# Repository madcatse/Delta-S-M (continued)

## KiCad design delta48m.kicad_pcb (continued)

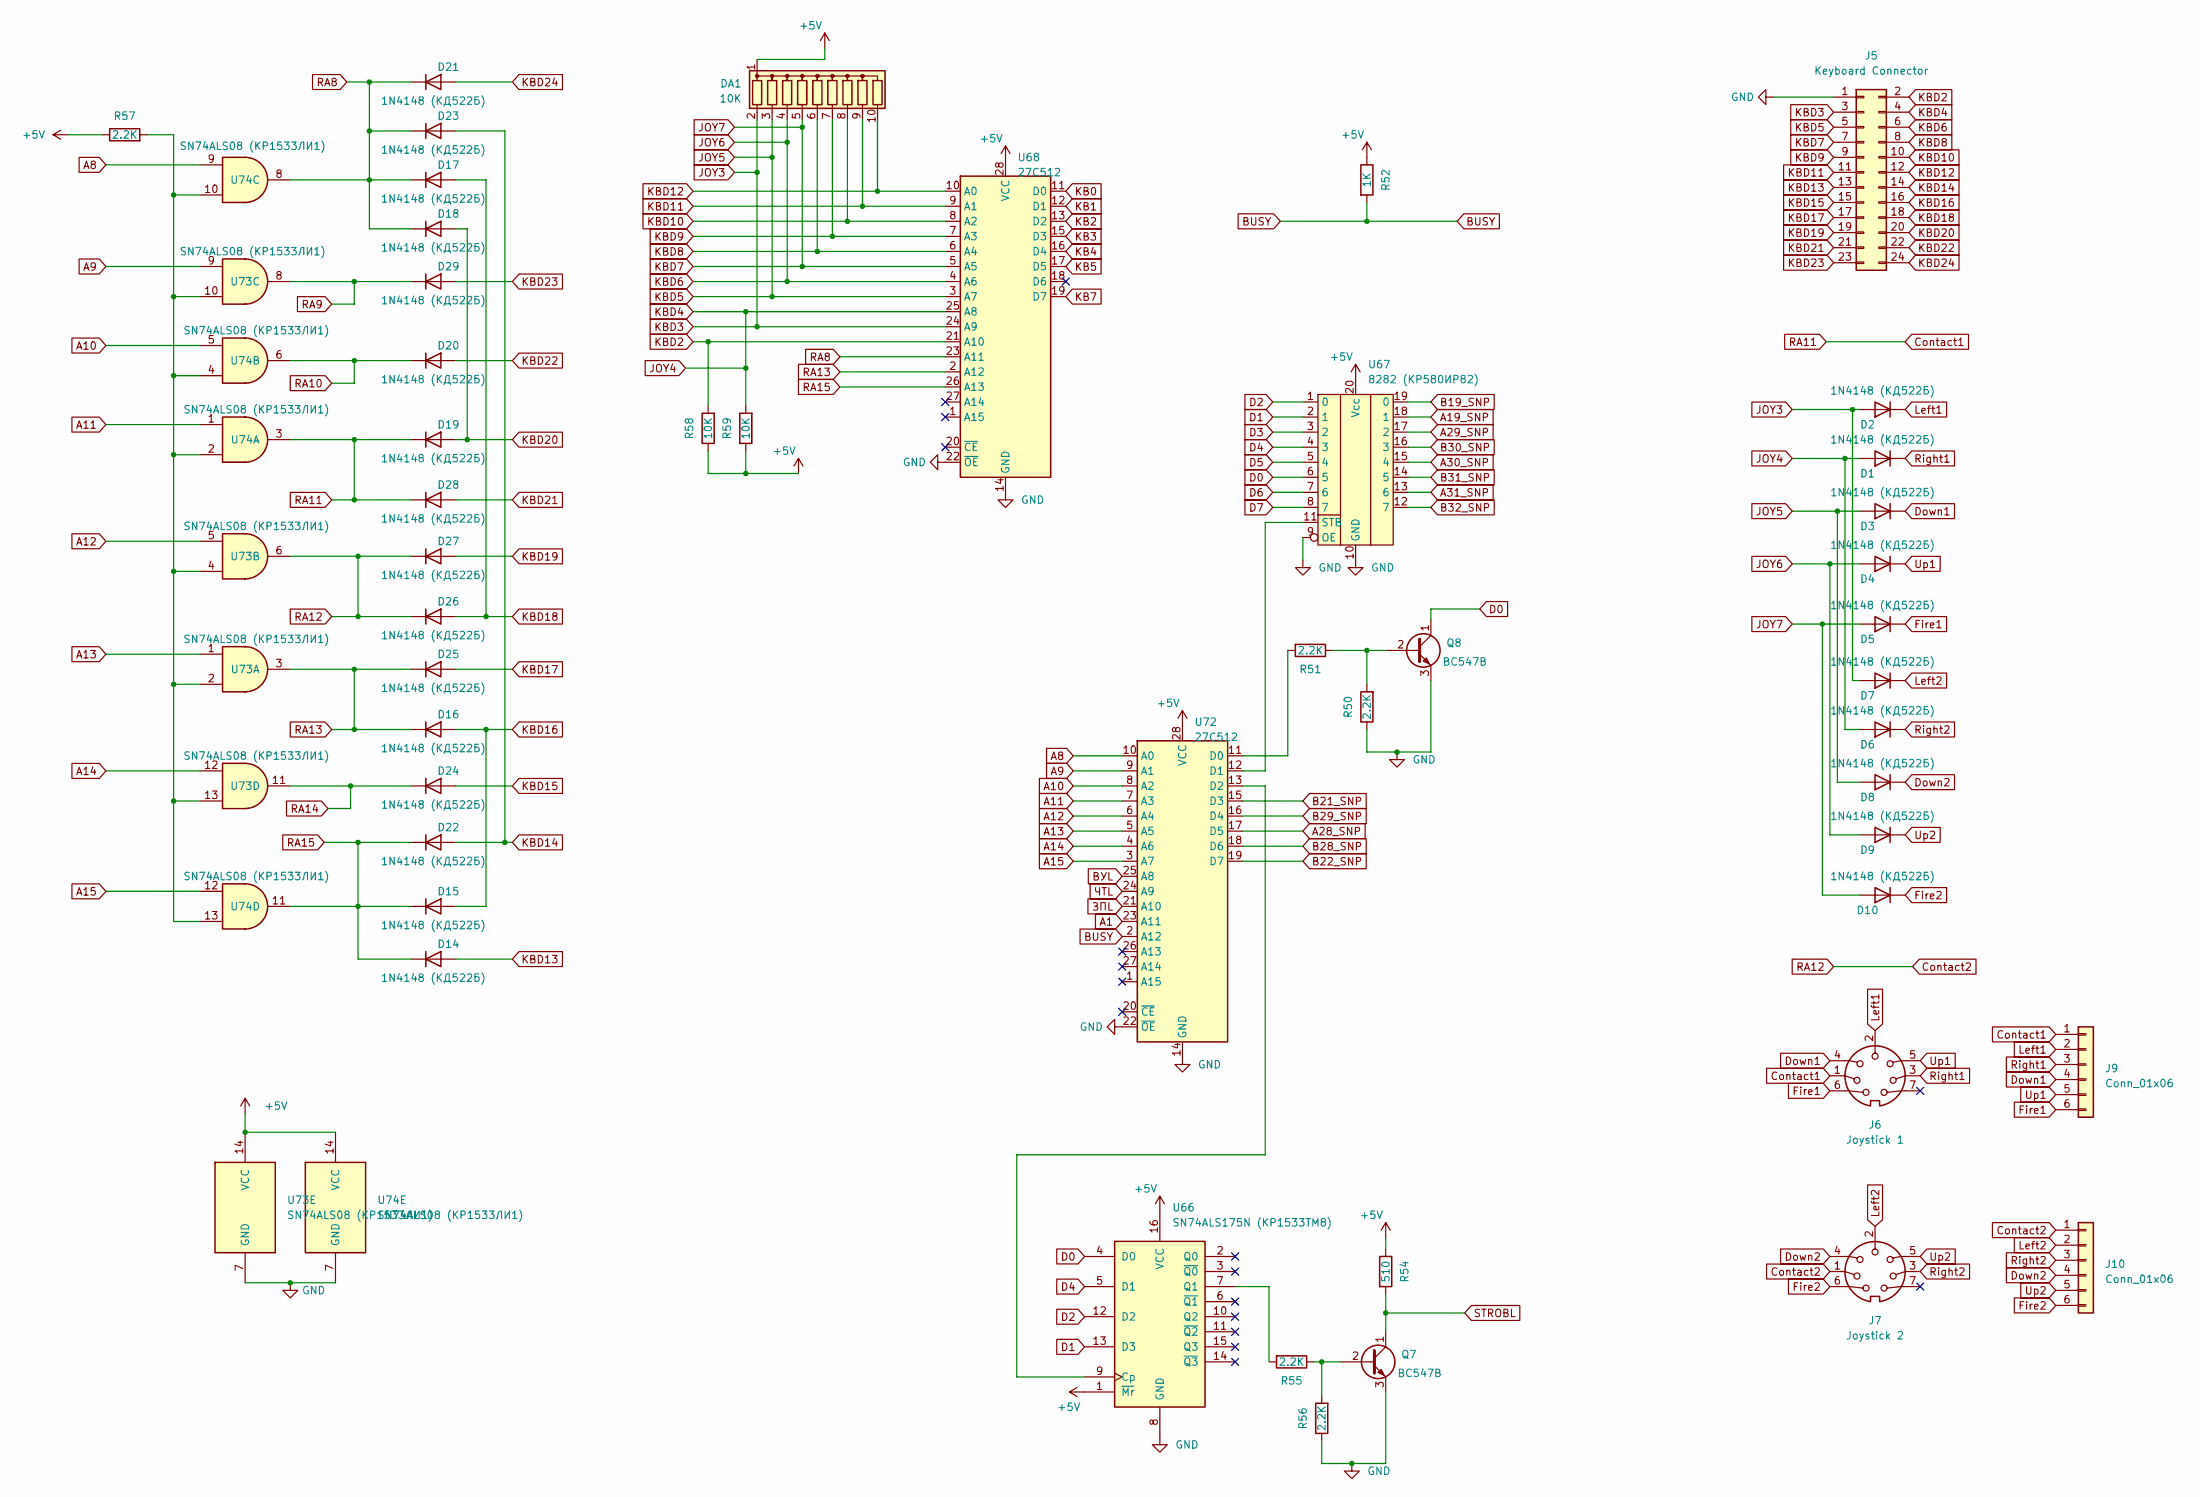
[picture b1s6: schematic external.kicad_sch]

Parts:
D1, D2, D3, D4, D5, D6, D7, D8, D9, D10, D14, D15, D16, D17, D18, D19, D20, D21, D22, D23, D24, D25, D26, D27, D28, D29: 1N4148 (КД522Б); D_DO-35_SOD27_P10.16mm_Horizontal
DA1: 10K; R_Array_SIP10
J5: Keyboard Connector; IDC-Header_2x12_P2.54mm_Vertical
J6: Joystick 1; DIN-7-Variable
J7: Joystick 2; DIN-7-Variable
J9, J10: Conn_01x06; PinHeader_1x06_P2.54mm_Vertical
Q7, Q8: BC547B; TO-92_Inline
R50, R51, R55, R56, R57: 2.2K; R_Axial_DIN0207_L6.3mm_D2.5mm_P10.16mm_Horizontal
R52: 1K; R_Axial_DIN0207_L6.3mm_D2.5mm_P10.16mm_Horizontal
R54: 510; R_Axial_DIN0207_L6.3mm_D2.5mm_P10.16mm_Horizontal
R58, R59: 10K; R_Axial_DIN0207_L6.3mm_D2.5mm_P10.16mm_Horizontal
U66: SN74ALS175N (КР1533ТМ8); DIP-16_W7.62mm_Socket
U67: 8282 (КР580ИР82); DIP-20_W7.62mm_Socket
U68, U72: 27C512; DIP-28_W15.24mm_Socket
U73, U74: SN74ALS08 (КР1533ЛИ1); DIP-14_W7.62mm_Socket

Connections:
+5V: DA1.1 (common), R52.1, R54.1, R57.1, R58.1, R59.1, U66.1 (~Mr), U66.16 (VCC), U67.20 (Vcc), U68.28 (VCC), U72.28 (VCC), U73.14 (VCC), U74.14 (VCC); also elsewhere on the board
A1: U72.23 (A11); also elsewhere on the board
A8: U72.10 (A0), U74.9; also elsewhere on the board
A9: U72.9 (A1), U73.9; also elsewhere on the board
A10: U72.8 (A2), U74.5; also elsewhere on the board
A11: U72.7 (A3), U74.1; also elsewhere on the board
A12: U72.6 (A4), U73.5; also elsewhere on the board
A13: U72.5 (A5), U73.1; also elsewhere on the board
A14: U72.4 (A6), U73.12; also elsewhere on the board
A15: U72.3 (A7), U74.12; also elsewhere on the board
A19_SNP: U67.18 (1); also elsewhere on the board
A28_SNP: U72.17 (D5); also elsewhere on the board
A29_SNP: U67.17 (2); also elsewhere on the board
A30_SNP: U67.15 (4); also elsewhere on the board
A31_SNP: U67.13 (6); also elsewhere on the board
B19_SNP: U67.19 (0); also elsewhere on the board
B21_SNP: U72.15 (D3); also elsewhere on the board
B22_SNP: U72.19 (D7); also elsewhere on the board
B28_SNP: U72.18 (D6); also elsewhere on the board
B29_SNP: U72.16 (D4); also elsewhere on the board
B30_SNP: U67.16 (3); also elsewhere on the board
B31_SNP: U67.14 (5); also elsewhere on the board
B32_SNP: U67.12 (7); also elsewhere on the board
BUSY: R52.2, U72.2 (A12); also elsewhere on the board
Contact1: D19.1 (K), D28.1 (K), J6.1, J9.1, U74.3
Contact2: D26.1 (K), D27.1 (K), J7.1, J10.1, U73.6
D0: Q8.1 (C), U66.4 (D0), U67.6 (5); also elsewhere on the board
D1: U66.13 (D3), U67.2 (1); also elsewhere on the board
D2: U66.12 (D2), U67.1 (0); also elsewhere on the board
D3: U67.3 (2); also elsewhere on the board
D4: U66.5 (D1), U67.4 (3); also elsewhere on the board
D5: U67.5 (4); also elsewhere on the board
D6: U67.7 (6); also elsewhere on the board
D7: U67.8 (7); also elsewhere on the board
Down1: D3.1 (K), J6.4, J9.4
Down2: D8.1 (K), J7.4, J10.4
Fire1: D5.1 (K), J6.6, J9.6
Fire2: D10.1 (K), J7.6, J10.6
GND: J5.1, Q7.3 (E), Q8.3 (E), R50.1, R56.1, U66.8 (GND), U67.9 (OE), U67.10 (GND), U68.14 (GND), U68.22 (~OE), U72.14 (GND), U72.22 (~OE), U73.7 (GND), U74.7 (GND); also elsewhere on the board
JOY3: D2.2 (A), D7.2 (A), DA1.2 (R1), J5.3, U68.24 (A9)
JOY4: D1.2 (A), D6.2 (A), J5.4, R59.2, U68.25 (A8)
JOY5: D3.2 (A), D8.2 (A), DA1.3 (R2), J5.5, U68.3 (A7)
JOY6: D4.2 (A), D9.2 (A), DA1.4 (R3), J5.6, U68.4 (A6)
JOY7: D5.2 (A), D10.2 (A), DA1.5 (R4), J5.7, U68.5 (A5)
KB0: U68.11 (D0); also elsewhere on the board
KB1: U68.12 (D1); also elsewhere on the board
KB2: U68.13 (D2); also elsewhere on the board
KB3: U68.15 (D3); also elsewhere on the board
KB4: U68.16 (D4); also elsewhere on the board
KB5: U68.17 (D5); also elsewhere on the board
KB7: U68.19 (D7); also elsewhere on the board
KBD2: J5.2, R58.2, U68.21 (A10)
KBD8: DA1.6 (R5), J5.8, U68.6 (A4)
KBD9: DA1.7 (R6), J5.9, U68.7 (A3)
KBD10: DA1.8 (R7), J5.10, U68.8 (A2)
KBD11: DA1.9 (R8), J5.11, U68.9 (A1)
KBD12: DA1.10 (R9), J5.12, U68.10 (A0)
KBD13: D14.2 (A), J5.13
KBD14: D22.2 (A), D23.2 (A), J5.14
KBD15: D24.2 (A), J5.15
KBD16: D15.2 (A), D16.2 (A), J5.16
KBD17: D25.2 (A), J5.17
KBD18: D17.2 (A), D26.2 (A), J5.18
KBD19: D27.2 (A), J5.19
KBD20: D18.2 (A), D19.2 (A), J5.20
KBD21: D28.2 (A), J5.21
KBD22: D20.2 (A), J5.22
KBD23: D29.2 (A), J5.23
KBD24: D21.2 (A), J5.24
Left1: D2.1 (K), J6.2, J9.2
Left2: D7.1 (K), J7.2, J10.2
unnamed: Q7.2 (B), R55.1, R56.2
unnamed: Q8.2 (B), R50.2, R51.1
unnamed: R57.2, U73.2, U73.4, U73.10, U73.13, U74.2, U74.4, U74.10, U74.13
unnamed: U66.9 (Cp), U72.13 (D2)
unnamed: R55.2, U66.7 (Q1)
unnamed: U67.11 (STB), U72.12 (D1)
unnamed: R51.2, U72.11 (D0)
RA8: D17.1 (K), D18.1 (K), D21.1 (K), D23.1 (K), U68.23 (A11), U74.8
RA9: D29.1 (K), U73.8
RA10: D20.1 (K), U74.6
RA13: D16.1 (K), D25.1 (K), U68.2 (A12), U73.3
RA14: D24.1 (K), U73.11
RA15: D14.1 (K), D15.1 (K), D22.1 (K), U68.26 (A13), U74.11
Right1: D1.1 (K), J6.3, J9.3
Right2: D6.1 (K), J7.3, J10.3
STROBL: Q7.1 (C), R54.2; also elsewhere on the board
Up1: D4.1 (K), J6.5, J9.5
Up2: D9.1 (K), J7.5, J10.5
ВУL: U72.25 (A8); also elsewhere on the board
ЗПL: U72.21 (A10); also elsewhere on the board
ЧТL: U72.24 (A9); also elsewhere on the board

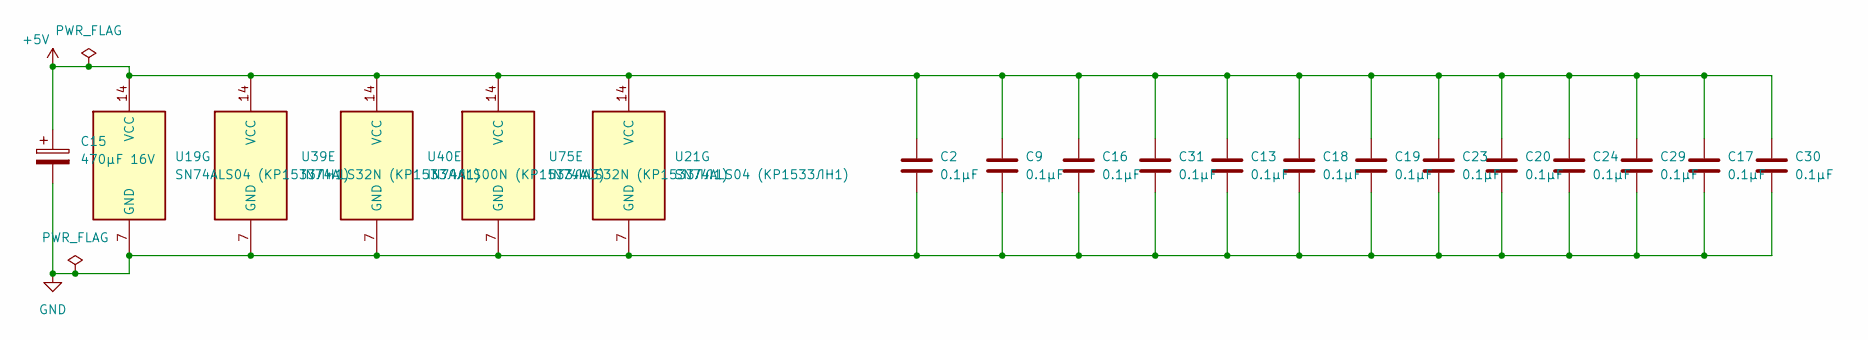
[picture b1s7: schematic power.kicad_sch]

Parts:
C2, C9, C13, C16, C17, C18, C19, C20, C23, C24, C29, C30, C31: 0.1μF; C_Disc_D7.0mm_W2.5mm_P5.00mm
C15: 470µF 16V; CP_Radial_D10.0mm_P5.00mm
U19, U21: SN74ALS04 (КР1533ЛН1); DIP-14_W7.62mm_Socket
U39, U75: IN74ALS32N (КР1533ЛЛ1); DIP-14_W7.62mm_Socket
U40: IN74ALS00N (КР1533ЛА3); DIP-14_W7.62mm_Socket

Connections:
+5V: C2.1, C9.1, C13.1, C15.1, C16.1, C17.1, C18.1, C19.1, C20.1, C23.1, C24.1, C29.1, C30.1, C31.1, U19.14 (VCC), U21.14 (VCC), U39.14 (VCC), U40.14 (VCC), U75.14 (VCC); also elsewhere on the board
GND: C2.2, C9.2, C13.2, C15.2, C16.2, C17.2, C18.2, C19.2, C20.2, C23.2, C24.2, C29.2, C30.2, C31.2, U19.7 (GND), U21.7 (GND), U39.7 (GND), U40.7 (GND), U75.7 (GND); also elsewhere on the board

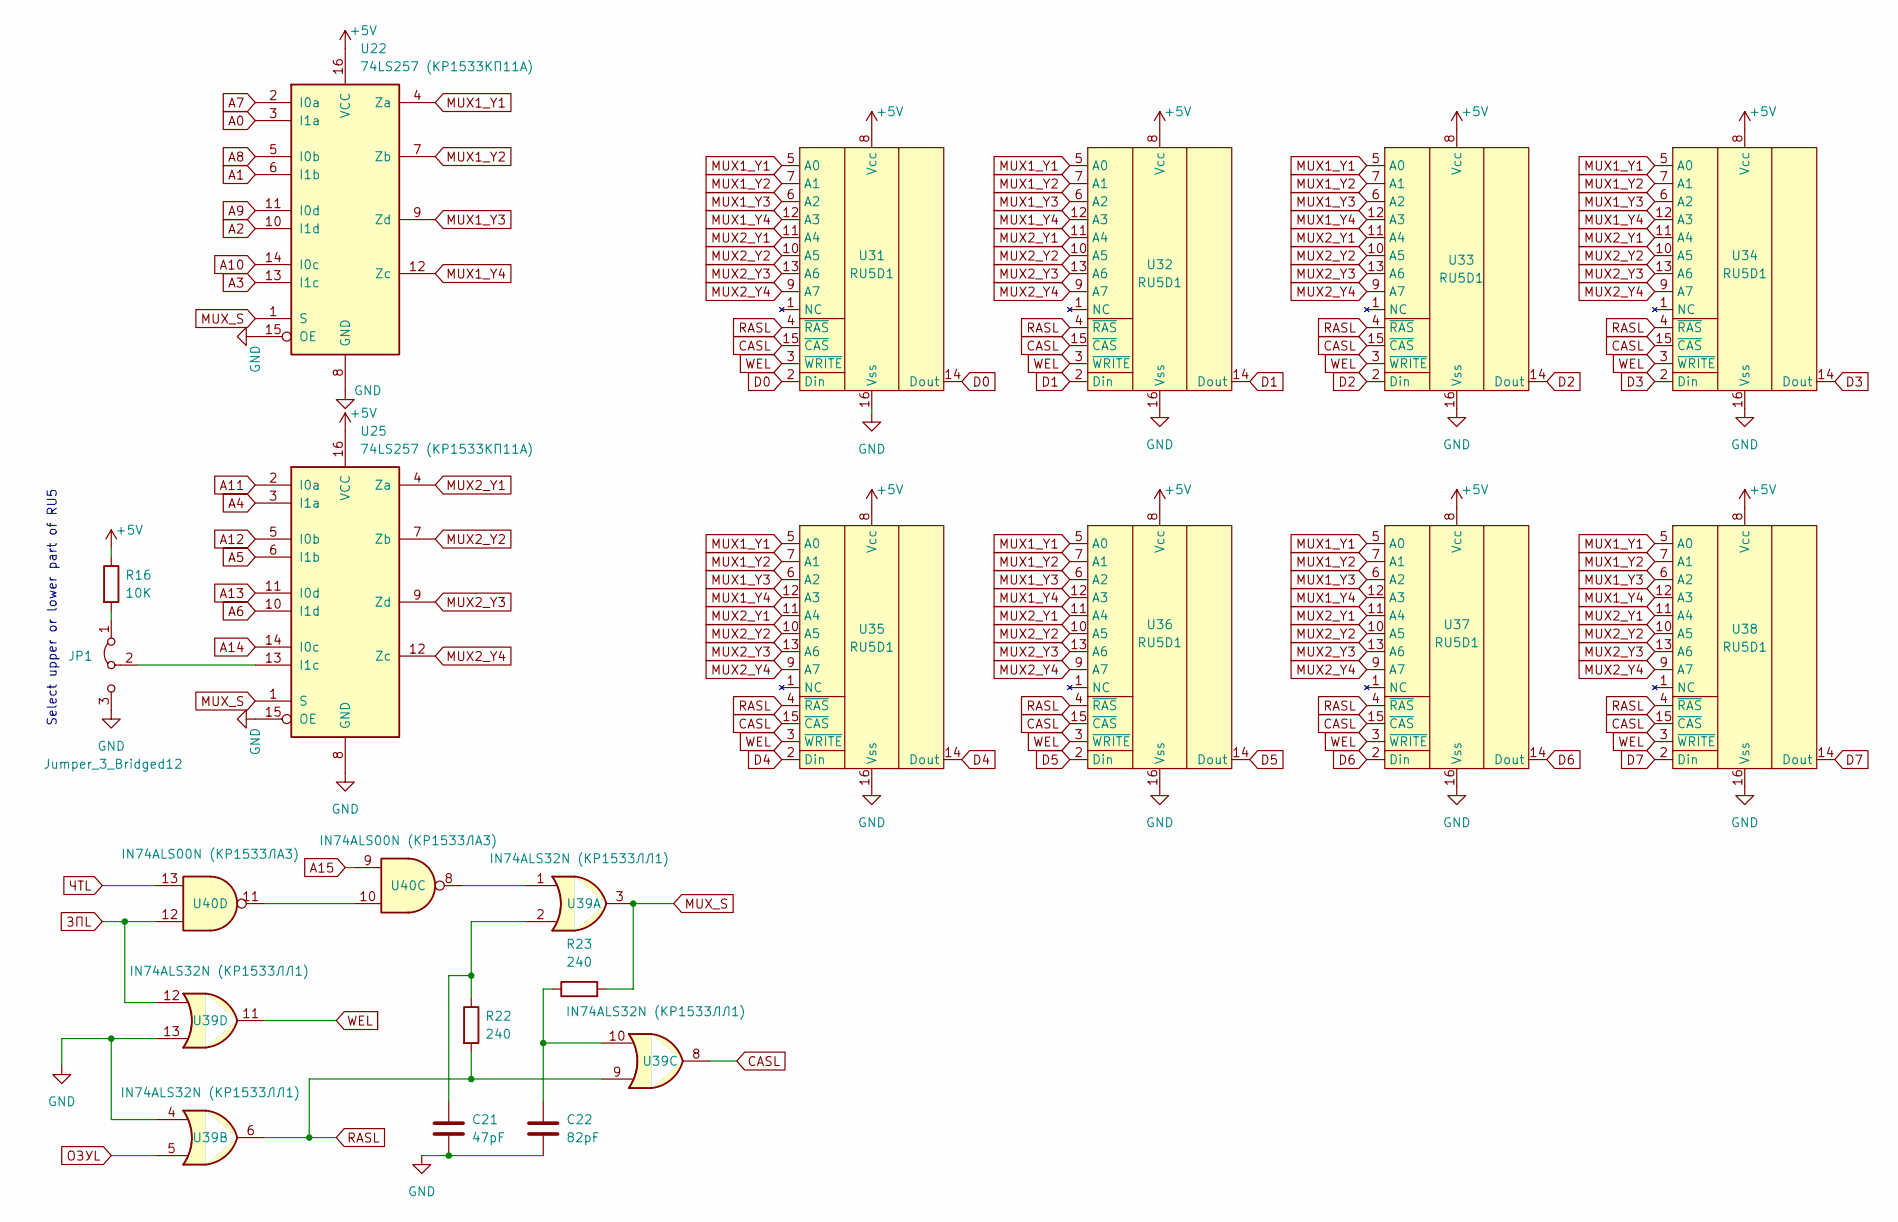
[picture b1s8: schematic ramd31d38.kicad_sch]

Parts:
C21: 47pF; C_Disc_D7.0mm_W2.5mm_P5.00mm
C22: 82pF; C_Disc_D7.0mm_W2.5mm_P5.00mm
JP1: Jumper_3_Bridged12; PinHeader_1x03_P2.54mm_Vertical
R16: 10K; R_Axial_DIN0207_L6.3mm_D2.5mm_P10.16mm_Horizontal
R22, R23: 240; R_Axial_DIN0207_L6.3mm_D2.5mm_P10.16mm_Horizontal
U22, U25: 74LS257 (КР1533КП11А); DIP-16_W7.62mm_Socket
U31, U32, U33, U34, U35, U36, U37, U38: RU5D1; DIP-16_W7.62mm_Socket
U39: IN74ALS32N (КР1533ЛЛ1); DIP-14_W7.62mm_Socket
U40: IN74ALS00N (КР1533ЛА3); DIP-14_W7.62mm_Socket

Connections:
+5V: R16.1, U22.16 (VCC), U25.16 (VCC), U31.8 (Vcc), U32.8 (Vcc), U33.8 (Vcc), U34.8 (Vcc), U35.8 (Vcc), U36.8 (Vcc), U37.8 (Vcc), U38.8 (Vcc); also elsewhere on the board
A0: U22.3 (I1a); also elsewhere on the board
A1: U22.6 (I1b); also elsewhere on the board
A2: U22.10 (I1d); also elsewhere on the board
A3: U22.13 (I1c); also elsewhere on the board
A4: U25.3 (I1a); also elsewhere on the board
A5: U25.6 (I1b); also elsewhere on the board
A6: U25.10 (I1d); also elsewhere on the board
A7: U22.2 (I0a); also elsewhere on the board
A8: U22.5 (I0b); also elsewhere on the board
A9: U22.11 (I0d); also elsewhere on the board
A10: U22.14 (I0c); also elsewhere on the board
A11: U25.2 (I0a); also elsewhere on the board
A12: U25.5 (I0b); also elsewhere on the board
A13: U25.11 (I0d); also elsewhere on the board
A14: U25.14 (I0c); also elsewhere on the board
A15: U40.9; also elsewhere on the board
CASL: U31.15 (~CAS), U32.15 (~CAS), U33.15 (~CAS), U34.15 (~CAS), U35.15 (~CAS), U36.15 (~CAS), U37.15 (~CAS), U38.15 (~CAS), U39.8
D0: U31.2 (Din), U31.14 (Dout); also elsewhere on the board
D1: U32.2 (Din), U32.14 (Dout); also elsewhere on the board
D2: U33.2 (Din), U33.14 (Dout); also elsewhere on the board
D3: U34.2 (Din), U34.14 (Dout); also elsewhere on the board
D4: U35.2 (Din), U35.14 (Dout); also elsewhere on the board
D5: U36.2 (Din), U36.14 (Dout); also elsewhere on the board
D6: U37.2 (Din), U37.14 (Dout); also elsewhere on the board
D7: U38.2 (Din), U38.14 (Dout); also elsewhere on the board
GND: C21.2, C22.2, JP1.3 (B), U22.8 (GND), U22.15 (OE), U25.8 (GND), U25.15 (OE), U31.16 (Vss), U32.16 (Vss), U33.16 (Vss), U34.16 (Vss), U35.16 (Vss), U36.16 (Vss), U37.16 (Vss), U38.16 (Vss), U39.4, U39.13; also elsewhere on the board
MUX1_Y1: U22.4 (Za), U31.5 (A0), U32.5 (A0), U33.5 (A0), U34.5 (A0), U35.5 (A0), U36.5 (A0), U37.5 (A0), U38.5 (A0)
MUX1_Y2: U22.7 (Zb), U31.7 (A1), U32.7 (A1), U33.7 (A1), U34.7 (A1), U35.7 (A1), U36.7 (A1), U37.7 (A1), U38.7 (A1)
MUX1_Y3: U22.9 (Zd), U31.6 (A2), U32.6 (A2), U33.6 (A2), U34.6 (A2), U35.6 (A2), U36.6 (A2), U37.6 (A2), U38.6 (A2)
MUX1_Y4: U22.12 (Zc), U31.12 (A3), U32.12 (A3), U33.12 (A3), U34.12 (A3), U35.12 (A3), U36.12 (A3), U37.12 (A3), U38.12 (A3)
MUX2_Y1: U25.4 (Za), U31.11 (A4), U32.11 (A4), U33.11 (A4), U34.11 (A4), U35.11 (A4), U36.11 (A4), U37.11 (A4), U38.11 (A4)
MUX2_Y2: U25.7 (Zb), U31.10 (A5), U32.10 (A5), U33.10 (A5), U34.10 (A5), U35.10 (A5), U36.10 (A5), U37.10 (A5), U38.10 (A5)
MUX2_Y3: U25.9 (Zd), U31.13 (A6), U32.13 (A6), U33.13 (A6), U34.13 (A6), U35.13 (A6), U36.13 (A6), U37.13 (A6), U38.13 (A6)
MUX2_Y4: U25.12 (Zc), U31.9 (A7), U32.9 (A7), U33.9 (A7), U34.9 (A7), U35.9 (A7), U36.9 (A7), U37.9 (A7), U38.9 (A7)
MUX_S: R23.2, U22.1 (S), U25.1 (S), U39.3
unnamed: C21.1, R22.1, U39.2
unnamed: C22.1, R23.1, U39.10
unnamed: JP1.1 (A), R16.2
unnamed: JP1.2 (C), U25.13 (I1c)
unnamed: U39.1, U40.8
unnamed: U40.10, U40.11
RASL: R22.2, U31.4 (~RAS), U32.4 (~RAS), U33.4 (~RAS), U34.4 (~RAS), U35.4 (~RAS), U36.4 (~RAS), U37.4 (~RAS), U38.4 (~RAS), U39.6, U39.9
WEL: U31.3 (~WRITE), U32.3 (~WRITE), U33.3 (~WRITE), U34.3 (~WRITE), U35.3 (~WRITE), U36.3 (~WRITE), U37.3 (~WRITE), U38.3 (~WRITE), U39.11
ЗПL: U39.12, U40.12; also elsewhere on the board
ОЗУL: U39.5; also elsewhere on the board
ЧТL: U40.13; also elsewhere on the board

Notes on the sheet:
Select upper or lower part of RU5

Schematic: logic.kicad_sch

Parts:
C1, C6, C8, C12: 120pF; C_Disc_D7.0mm_W2.5mm_P5.00mm
C3: 220pF; C_Disc_D7.0mm_W2.5mm_P5.00mm
C4, C5: 1000pF; C_Disc_D7.0mm_W2.5mm_P5.00mm
C32: 82pF; C_Disc_D7.0mm_W2.5mm_P5.00mm
R1, R2: 470; R_Axial_DIN0207_L6.3mm_D2.5mm_P10.16mm_Horizontal
R4, R8, R9, R13: 160; R_Axial_DIN0207_L6.3mm_D2.5mm_P10.16mm_Horizontal
R5, R6: 10K; R_Axial_DIN0207_L6.3mm_D2.5mm_P10.16mm_Horizontal
R10: 330; R_Axial_DIN0207_L6.3mm_D2.5mm_P10.16mm_Horizontal
R15: 510; R_Axial_DIN0207_L6.3mm_D2.5mm_P10.16mm_Horizontal
R19: 180; R_Axial_DIN0207_L6.3mm_D2.5mm_P10.16mm_Horizontal
U1, U10: SN74ALS08 (КР1533ЛИ1); DIP-14_W7.62mm_Socket
U2, U7, U19, U49: SN74ALS04 (КР1533ЛН1); DIP-14_W7.62mm_Socket
U3, U20: SN74ALS74AN (КР1533ТМ2); DIP-14_W7.62mm_Socket
U4: SN74ALS193N_(КР1533ИЕ7); DIP-16_W7.62mm_Socket
U5: СD4013АN_(К561ТМ2); DIP-14_W7.62mm_Socket
U6: CD4015A (К561ИР2); DIP-16_W7.62mm_Socket
U8, U9: СD4001АN (К561ЛЕ5); DIP-14_W7.62mm_Socket
U11: IN74ALS00N (КР1533ЛА3); DIP-14_W7.62mm_Socket
U12: IN74ALS02N (КР1533ЛЕ1); DIP-14_W7.62mm_Socket
U13: SN74ALS10 (КР1533ЛА4); DIP-14_W7.62mm_Socket
U14: SN74ALS86N (КР1533ЛП5); DIP-14_W7.62mm_Socket
U15, U17: CD4520АN (К561ИЕ10A); DIP-16_W7.62mm_Socket
U16: SN74ALS257N_(КР1533КП11А); DIP-16_W7.62mm_Socket
U18: CD4011 (К561ЛА7); DIP-14_W7.62mm_Socket
U28: IN74ALS32N (КР1533ЛЛ1); DIP-14_W7.62mm_Socket
Y1: 14 MHz; Crystal_HC49-U_Vertical

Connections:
7MHZ: U3.2 (D), U3.6 (~Q), U3.11 (C), U11.5; also elsewhere on the board
+5V: R15.2, U1.14 (VCC), U2.14 (VCC), U3.1 (~R), U3.4 (~S), U3.10 (~S), U3.13 (~R), U3.14 (VCC), U4.4 (DOWN), U4.11 (~LOAD), U4.16 (VCC), U5.14 (Ucc), U6.16 (Vdd), U7.14 (VCC), U8.14 (VDD), U9.14 (VDD), U10.14 (VCC), U11.14 (VCC), U13.14 (VCC), U14.10, U15.10 (Enable), U16.16 (VCC), U17.16 (VDD), U18.14 (VDD), U20.1 (~R), U20.14 (VCC), U28.14 (VCC); also elsewhere on the board
BA0: U4.7 (QD), U13.4, U14.4, U15.9 (CK), U20.11 (C); also elsewhere on the board
BA1: U5.11 (C2), U15.11 (Q1); also elsewhere on the board
BA2: R4.1, R5.1, U15.12 (Q2); also elsewhere on the board
BA3: U15.13 (Q3); also elsewhere on the board
BA4: U5.4 (R1), U6.7 (D), U15.14 (Q4); also elsewhere on the board
BA5: U6.1 (CP), U9.9, U17.2 (Enable), U17.14 (Q4); also elsewhere on the board
BA6: U17.3 (Q1); also elsewhere on the board
BA7: U17.4 (Q2); also elsewhere on the board
BA8: U16.7 (Zb); also elsewhere on the board
BA9: U16.4 (Za); also elsewhere on the board
BA10: U16.9 (Zd); also elsewhere on the board
BA11: U16.12 (Zc); also elsewhere on the board
BA12: U28.8; also elsewhere on the board
BCASL: U1.6; also elsewhere on the board
BMX: U14.11; also elsewhere on the board
BRASL: R9.1, U1.11; also elsewhere on the board
CCML: U17.10 (Enable), U18.10; also elsewhere on the board
CT4: U16.10 (I1d), U17.13 (Q3), U18.13
CT9: U16.2 (I0a), U17.6 (Q4), U18.6, U28.10
GND: C3.1, C4.1, C5.1, C6.1, C8.1, C12.2, C32.1, U1.7 (GND), U2.7 (GND), U3.7 (GND), U4.1 (B), U4.8 (GND), U4.9 (D), U4.10 (C), U4.14 (CLR), U4.15 (A), U5.6 (S1), U5.7 (GND), U5.8 (S2), U5.10 (R2), U6.8 (Vss), U6.14 (MR), U7.7 (GND), U8.7 (VSS), U9.7 (VSS), U10.7 (GND), U11.7 (GND), U13.7 (GND), U14.13, U16.8 (GND), U16.11 (I0d), U16.15 (OE), U17.1 (CK), U17.8 (VSS), U17.9 (CK), U18.7 (VSS), U20.7 (GND), U28.7 (GND); also elsewhere on the board
KGIL: U9.4, U18.1
KKADRAN: U9.11, U17.7 (Reset), U17.15 (Reset), U19.9
KRAIN: U19.12; also elsewhere on the board
KSGIN: U18.3; also elsewhere on the board
unnamed: C1.1, R2.2, U2.6
unnamed: C1.2, R1.1, U2.9
unnamed: C3.2, R4.2, U7.1
unnamed: C4.2, U7.8, U8.8
unnamed: C5.2, R6.1, U9.12
unnamed: C6.2, R10.2, U2.3
unnamed: C8.2, R19.2, U14.9
unnamed: C12.1, R13.1, U19.13
unnamed: C32.2, R8.2, U1.4
unnamed: R2.1, U2.5, Y1.1
unnamed: R6.2, U7.6
unnamed: R8.1, U1.13, U14.8
unnamed: R9.2, U14.12
unnamed: R10.1, U13.8, U19.3
unnamed: U1.5, U11.11
unnamed: U1.10, U2.2
unnamed: R1.2, U2.8, U3.3 (C), Y1.2
unnamed: U1.12, U3.12 (D), U13.12
unnamed: U4.3 (QA), U11.4, U11.10, U12.5, U19.5
unnamed: U4.2 (QB), U11.9, U12.6
unnamed: U1.9, U4.6 (QC), U13.5, U14.5
unnamed: R5.2, U5.3 (C1)
unnamed: U5.5 (D1), U6.3 (Q3), U8.5
unnamed: U5.1 (Q1), U5.9 (D2), U18.9
unnamed: U5.12 (Q2o), U18.2
unnamed: U6.9 (CP), U7.2, U18.8
unnamed: U6.10 (Q4), U7.9, U8.6, U8.9
unnamed: U6.15 (D), U7.13, U18.4
unnamed: U6.13 (Q1), U9.2
unnamed: U6.11 (Q3), U8.12
unnamed: U6.2 (Q4), U7.3, U9.1
unnamed: U7.4, U7.5, U8.1, U8.13, U9.13
unnamed: U7.10, U9.8
unnamed: U7.11, U8.11
unnamed: U7.12, U8.2
unnamed: U9.3, U9.5
unnamed: U10.1, U19.6
unnamed: U10.3, U49.1
unnamed: U8.3, U10.4
unnamed: U8.4, U10.5
unnamed: U10.13, U13.6
unnamed: U2.1, U11.8, U13.2, U13.3
unnamed: U11.6, U11.12
unnamed: U2.13, U12.4
unnamed: U2.12, U13.9, U13.10
unnamed: U13.11, U13.13, U14.6
unnamed: U6.6 (MR), U8.10, U15.15 (Reset)
unnamed: U16.5 (I0b), U16.13 (I1c), U17.5 (Q3), U18.5
unnamed: U16.3 (I1a), U17.12 (Q2)
unnamed: U16.6 (I1b), U17.11 (Q1)
unnamed: U9.6, U9.10, U18.12
unnamed: U19.10, U28.9
unnamed: U3.5 (Q), U4.5 (UP), U20.3 (C)
unnamed: U10.2, U20.5 (Q)
unnamed: U10.11, U20.4 (~S)
unnamed: U10.6, U10.12, U13.1, U20.12 (D)
unnamed: R13.2, U20.9 (Q)
unnamed: U20.10 (~S), U20.13 (~R)
OZUMPN: R19.1; also elsewhere on the board
TAIMS: U18.11; also elsewhere on the board
UPRMX: U16.1 (S), U19.4, U19.11
VOZUL: U20.2 (D); also elsewhere on the board
ZPRGAT+: U2.4; also elsewhere on the board
ZPRGBD: U3.8 (~Q), U11.13; also elsewhere on the board
ZPVDN: U1.8; also elsewhere on the board
ПРL: U19.8; also elsewhere on the board
ТАКТ: R15.1, U49.2; also elsewhere on the board

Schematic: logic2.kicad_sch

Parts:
C10, C11: 0.1µF; C_Disc_D7.0mm_W2.5mm_P5.00mm
C14: 4.7µF 16V; CP_Radial_D4.0mm_P2.00mm
D11, D12, D13, D30, D31: 1N4148 (КД522Б); D_DO-35_SOD27_P10.16mm_Horizontal
JP4, JP5: Jumper_2_Open; PinHeader_1x02_P2.54mm_Vertical
R11: 39K; R_Axial_DIN0207_L6.3mm_D2.5mm_P10.16mm_Horizontal
R12: 100K; R_Axial_DIN0207_L6.3mm_D2.5mm_P10.16mm_Horizontal
R20: 560; R_Axial_DIN0207_L6.3mm_D2.5mm_P10.16mm_Horizontal
R21: 10K; R_Axial_DIN0207_L6.3mm_D2.5mm_P10.16mm_Horizontal
R32, R35, R36, R39: 470; R_Axial_DIN0207_L6.3mm_D2.5mm_P10.16mm_Horizontal
R34, R38, R41: 2.7K; R_Axial_DIN0207_L6.3mm_D2.5mm_P10.16mm_Horizontal
R45, R46: 1K; R_Axial_DIN0207_L6.3mm_D2.5mm_P10.16mm_Horizontal
U12, U30: IN74ALS02N (КР1533ЛЕ1); DIP-14_W7.62mm_Socket
U14, U50: SN74ALS86N (КР1533ЛП5); DIP-14_W7.62mm_Socket
U15: CD4520АN (К561ИЕ10A); DIP-16_W7.62mm_Socket
U21, U49: SN74ALS04 (КР1533ЛН1); DIP-14_W7.62mm_Socket
U29: IN74ALS32N (КР1533ЛЛ1); DIP-14_W7.62mm_Socket
U40: IN74ALS00N (КР1533ЛА3); DIP-14_W7.62mm_Socket
U51: SN7486N (К155ЛП5); DIP-14_W7.62mm_Socket
U52, U56, U59, U63: SN74ALS175N (КР1533ТМ8); DIP-16_W7.62mm_Socket
U53, U60: SN74ALS153N (КР1533КП2); DIP-16_W7.62mm_Socket
U54, U61: SN74ALS298N (КР1533КП13); DIP-16_W7.62mm_Socket
U55, U62: 74LS257 (КР1533КП11А); DIP-16_W7.62mm_Socket
U57, U58, U64, U65: SN74LS295N_(К555ИР16); DIP-14_W7.62mm_Socket

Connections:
7MHZ: U54.11 (Cp), U58.9 (Cp), U61.11 (Cp), U65.9 (Cp); also elsewhere on the board
+5V: R45.2, R46.2, U12.14 (VCC), U14.14 (VCC), U15.2 (Enable), U15.16 (VDD), U29.14 (VCC), U30.14 (VCC), U49.14 (VCC), U50.14 (VCC), U51.14 (VCC), U52.1 (~Mr), U52.16 (VCC), U53.16 (VCC), U54.16 (VCC), U55.16 (VCC), U56.1 (~Mr), U56.16 (VCC), U57.6 (Pe), U57.8 (OE), U57.14 (VCC), U58.8 (OE), U58.14 (VCC), U59.1 (~Mr), U59.16 (VCC), U60.16 (VCC), U61.16 (VCC), U62.16 (VCC), U63.1 (~Mr), U63.16 (VCC), U64.6 (Pe), U64.8 (OE), U64.14 (VCC), U65.8 (OE), U65.14 (VCC); also elsewhere on the board
A0: U12.3; also elsewhere on the board
A14: U49.5; also elsewhere on the board
A15: U29.1; also elsewhere on the board
BD0: U62.14 (I0c), U63.4 (D0), U64.2 (P0); also elsewhere on the board
BD1: U62.2 (I0a), U63.5 (D1), U64.3 (P1); also elsewhere on the board
BD2: U62.5 (I0b), U63.12 (D2), U64.4 (P2); also elsewhere on the board
BD3: U55.2 (I0a), U63.13 (D3), U64.5 (P3); also elsewhere on the board
BD4: U56.4 (D0), U57.2 (P0), U62.11 (I0d); also elsewhere on the board
BD5: U55.5 (I0b), U56.5 (D1), U57.3 (P1); also elsewhere on the board
BD6: U55.11 (I0d), U56.12 (D2), U57.4 (P2); also elsewhere on the board
BD7: U55.14 (I0c), U56.13 (D3), U57.5 (P3); also elsewhere on the board
BWEL: U40.3; also elsewhere on the board
CCML: U14.2; also elsewhere on the board
CHTRGL: U29.8, U55.15 (OE), U62.15 (OE)
D0: U52.4 (D0), U62.12 (Zc); also elsewhere on the board
D1: U52.12 (D1), U62.4 (Za); also elsewhere on the board
D2: U52.13 (D2), U62.7 (Zb); also elsewhere on the board
D3: U55.4 (Za), U59.4 (D0); also elsewhere on the board
D4: U52.5 (D3), U62.9 (Zd); also elsewhere on the board
D5: U55.7 (Zb); also elsewhere on the board
D6: U55.9 (Zd); also elsewhere on the board
D7: U55.12 (Zc); also elsewhere on the board
GND: JP4.2 (B), JP5.2 (B), U12.7 (GND), U14.7 (GND), U15.7 (Reset), U15.8 (VSS), U29.7 (GND), U30.5, U30.7 (GND), U49.7 (GND), U50.7 (GND), U51.7 (GND), U52.8 (GND), U53.8 (GND), U53.12 (I2b), U53.13 (I3b), U54.8 (GND), U55.8 (GND), U56.8 (GND), U57.7 (GND), U58.7 (GND), U59.8 (GND), U60.8 (GND), U61.8 (GND), U62.8 (GND), U63.8 (GND), U64.7 (GND), U65.1 (Ds), U65.7 (GND); also elsewhere on the board
KB0: U62.13 (I1c); also elsewhere on the board
KB1: U62.3 (I1a); also elsewhere on the board
KB2: U62.6 (I1b); also elsewhere on the board
KB3: U55.3 (I1a); also elsewhere on the board
KB4: U62.10 (I1d); also elsewhere on the board
KB5: U55.6 (I1b); also elsewhere on the board
KB7: U55.13 (I1c); also elsewhere on the board
KRAIN: U53.2 (S1), U60.2 (S1); also elsewhere on the board
KSGIN: U53.1 (Ea), U53.15 (Eb), U60.1 (Ea), U60.15 (Eb); also elsewhere on the board
MAG: R12.2, U21.6, U55.10 (I1d)
MAG_IN: R20.1; also elsewhere on the board
MAG_OUT: R21.2; also elsewhere on the board
unnamed: C10.1, R11.2, U21.4
unnamed: C10.2, R12.1, U21.5
unnamed: C11.2, R11.1, U21.3
unnamed: C14.2, R20.2
unnamed: D11.1 (K), R34.2
unnamed: D12.1 (K), R38.2
unnamed: D13.1 (K), R41.2
unnamed: C14.1, D30.2 (A), D31.1 (K), U21.1
unnamed: C11.1, D30.1 (K), D31.2 (A), U21.2
unnamed: JP4.1 (A), R46.1, U51.1
unnamed: JP5.1 (A), R45.1, U51.5, U51.10, U51.13
unnamed: R32.1, U51.6
unnamed: R35.1, U51.3
unnamed: R36.1, U51.8
unnamed: R39.1, U51.11
unnamed: U14.3, U49.13
unnamed: U15.6 (Q4), U40.5
unnamed: U29.2, U49.6
unnamed: U29.10, U30.1
unnamed: U29.3, U29.12, U30.12
unnamed: U30.4, U40.2
unnamed: U30.8, U49.8
unnamed: U40.6, U50.9
unnamed: U49.12, U51.2
unnamed: U52.2 (Q0), U60.3 (I3a), U60.4 (I2a)
unnamed: U52.10 (Q2), U60.12 (I2b), U60.13 (I3b)
unnamed: U52.15 (Q3), U53.3 (I3a), U53.4 (I2a)
unnamed: U53.6 (I0a), U61.9 (I0c), U61.13 (Qc)
unnamed: U53.10 (I0b), U53.11 (I1b), U54.9 (I0c), U54.13 (Qc)
unnamed: U53.5 (I1a), U54.7 (I0d), U54.12 (Qd)
unnamed: U50.8, U53.14 (S0), U60.14 (S0)
unnamed: U51.12, U53.7 (Za)
unnamed: R34.1, R38.1, R41.1, U53.9 (Zb)
unnamed: U54.3 (I0a), U54.15 (Qa), U60.11 (I1b)
unnamed: U40.4, U54.4 (I0b), U54.14 (Qb)
unnamed: U54.2 (I1a), U56.2 (Q0)
unnamed: U54.1 (I1b), U56.15 (Q3)
unnamed: U54.5 (I1c), U56.10 (Q2)
unnamed: U54.6 (I1d), U56.7 (Q1)
unnamed: U57.13 (Q0), U58.2 (P0)
unnamed: U57.12 (Q1), U58.3 (P1)
unnamed: U57.11 (Q2), U58.4 (P2)
unnamed: U57.10 (Q3), U58.5 (P3)
unnamed: U58.1 (Ds), U65.10 (Q3)
unnamed: U50.10, U58.10 (Q3)
unnamed: R21.1, U59.2 (Q0)
unnamed: U60.6 (I0a), U61.3 (I0a), U61.15 (Qa)
unnamed: U60.10 (I0b), U61.7 (I0d), U61.12 (Qd)
unnamed: U60.5 (I1a), U61.4 (I0b), U61.14 (Qb)
unnamed: U51.9, U60.7 (Za)
unnamed: U51.4, U60.9 (Zb)
unnamed: U61.2 (I1a), U63.2 (Q0)
unnamed: U61.1 (I1b), U63.15 (Q3)
unnamed: U61.5 (I1c), U63.10 (Q2)
unnamed: U61.6 (I1d), U63.7 (Q1)
unnamed: U64.13 (Q0), U65.2 (P0)
unnamed: U64.12 (Q1), U65.3 (P1)
unnamed: U64.11 (Q2), U65.4 (P2)
unnamed: U64.10 (Q3), U65.5 (P3)
OZUMPN: U29.13, U30.2, U30.13, U40.1; also elsewhere on the board
SYNCRO: R35.2; also elsewhere on the board
TAIMS: U14.1, U15.1 (CK); also elsewhere on the board
UZVUK: U52.7 (Q1); also elsewhere on the board
VIBOZUL: U12.1, U30.3, U49.9, U55.1 (S), U62.1 (S)
VOZUL: U29.11; also elsewhere on the board
YB: D13.2 (A), R39.2; also elsewhere on the board
YG: D12.2 (A), R36.2; also elsewhere on the board
YR: D11.2 (A), R32.2; also elsewhere on the board
ZPRG+: U30.10, U52.9 (Cp), U59.9 (Cp)
ZPRGAT+: U56.9 (Cp), U63.9 (Cp); also elsewhere on the board
ZPRGBD: U57.9 (Cp), U64.9 (Cp); also elsewhere on the board
ZPVDN: U54.10 (S), U58.6 (Pe), U61.10 (S), U65.6 (Pe); also elsewhere on the board
ВУL: U12.2; also elsewhere on the board
ЗПL: U30.6, U30.9; also elsewhere on the board
ОЗУL: U30.11; also elsewhere on the board
ЧТL: U29.9; also elsewhere on the board

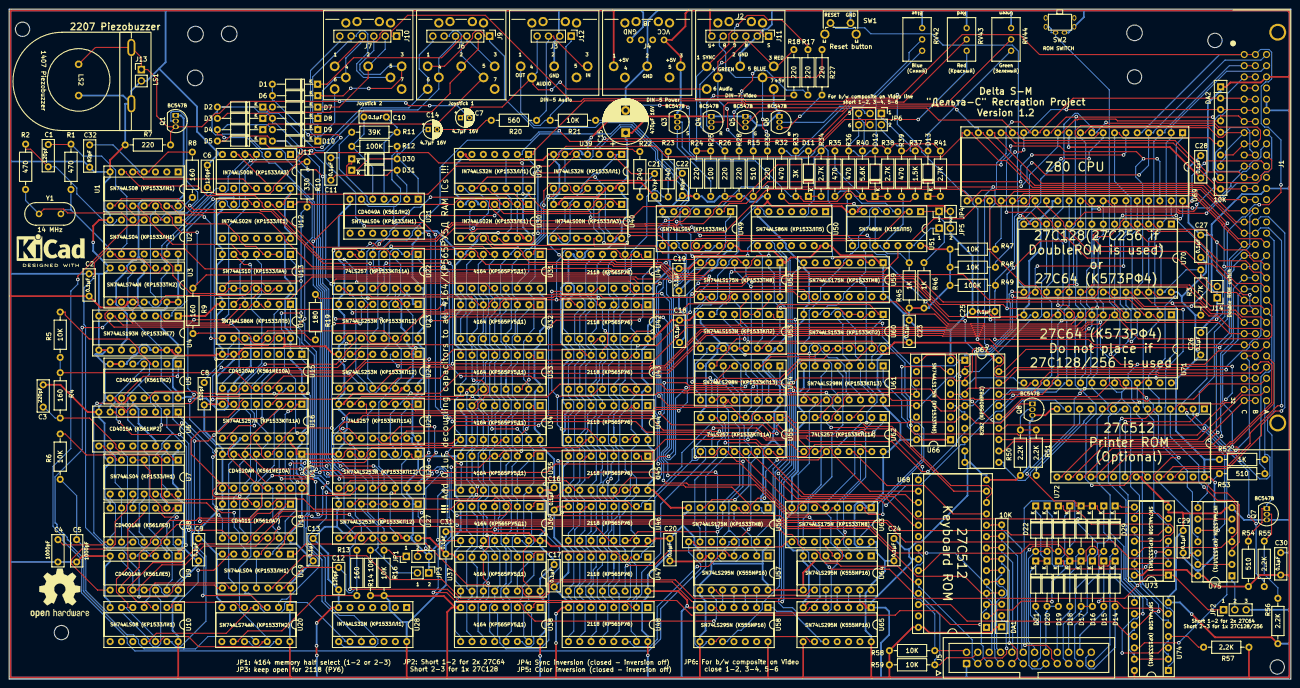
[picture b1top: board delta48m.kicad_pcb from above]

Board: 2 copper layers, 287.0 x 150.0 mm, 240 parts (0 on the bottom side), 329 nets.

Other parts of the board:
H1, H7, H10: MountingHole_3.5mm
H3, H4, H5, H6, H9: MountingHole_3.2mm_M3
H8: MountingHole_3mm
Log1: KiCad-Logo2_6mm_SilkScreen
Log2: OSHW-Logo2_14.6x12mm_SilkScreen

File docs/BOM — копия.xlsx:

Reference | Value | Datasheet | РљРѕР».
C1, C6, C8, C12 | 120pF | ~ | 4
C2, C9, C13, C16-C20, C23-C31 | 0.1μF | ~ | 17
C3 | 220pF | ~ | 1
C4, C5 | 1000pF | ~ | 2
C10, C11 | 0.1µF | ~ | 2
C14 | 4.7µF 15V | ~ | 1
C15 | 470µF | ~ | 1
C21 | 47pF | ~ | 1
C22, C32 | 82pF | ~ | 2
D1-D31 | 1N4148 (КД522Б) | ~ | 31
DA1, DA2, R5, R6, R14, R16, R21, R47, R48, R58, R59 | 10K | -- СЃРјРµС€Р°РЅРЅС‹Рµ Р·РЅР°С‡РµРЅРёСЏ -- | 11
J1 | SNP |  | 1
J2 | DIN-7 Video | http://www.mouser.com/ds/2/18/40_c091_abd_e-75918.pdf | 1
J3 | DIN-5 Audio | http://www.mouser.com/ds/2/18/40_c091_abd_e-75918.pdf | 1
J4 | DIN-5 Power | http://www.mouser.com/ds/2/18/40_c091_abd_e-75918.pdf | 1
J5 | Keyboard Connector | ~ | 1
J6 | Joystick 1 | http://www.mouser.com/ds/2/18/40_c091_abd_e-75918.pdf | 1
J7 | Joystick 2 | http://www.mouser.com/ds/2/18/40_c091_abd_e-75918.pdf | 1
J8 | RGB/Composite | ~ | 1
JP1 | Jumper_3_Bridged12 | ~ | 1
JP2 | Jumper_3_Open | ~ | 1
JP3 | Jumper_2_Open | ~ | 1
LS1 | Speaker | ~ | 1
Q1, Q3-Q8 | BC547B | https://www.onsemi.com/pub/Collateral/BC550-D.pdf | 7
R1, R32, R35, R36, R39 | 470 | ~ | 5
R2 | 430 | ~ | 1
R4, R8, R9, R13 | 160 | ~ | 4
R7, R24, R26, R28, R30 | 220 | ~ | 5
R10 | 330 | ~ | 1
R11 | 39K | ~ | 1
R12, R49 | 100K | ~ | 2
R15, R53, R54 | 510 | ~ | 3
R19 | 180 | ~ | 1
R20 | 560 | ~ | 1
R22, R23 | 240 | ~ | 2
R25 | 100 | ~ | 1
R33 | 3K | ~ | 1
R34, R38, R41 | 2.7K | ~ | 3
R37 | 1.5K | ~ | 1
R40 | 5.6K | ~ | 1
R45, R46, R52 | 1K | ~ | 3
R50, R51, R55-R57 | 2.2K | ~ | 5
RV42-RV44 | 22K | ~ | 3
SW1 | Reset button | ~ | 1
U1, U10, U73, U74 | SN74ALS08 (КР1533ЛИ1) | http://www.ti.com/lit/gpn/sn74LS08 | 4
U2, U7, U19, U49 | SN74ALS04 (КР1533ЛН1) | http://www.ti.com/lit/gpn/sn74LS04 | 4
U3, U20 | SN74ALS74AN (КР1533ТМ2) | 74xx/74hc_hct74.pdf | 2
U4 | SN74ALS193N_(КР1533ИЕ7) | http://www.ti.com/lit/ds/symlink/sn74ls193.pdf | 1
U5 | СD4013АN_(К561ТМ2) |  | 1
U6 | CD4015A (К561ИР2) |  | 1
U8, U9 | СD4001АN (К561ЛЕ5) | http://www.intersil.com/content/dam/Intersil/documents/cd40/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 | 2
U11, U40 | IN74ALS00N (КР1533ЛА3) | http://www.ti.com/lit/gpn/sn74ls00 | 2
U12, U30 | IN74ALS02N (КР1533ЛЕ1) | http://www.ti.com/lit/gpn/sn74ls02 | 2
U13 | SN74ALS10 (КР1533ЛА4) | http://www.ti.com/lit/gpn/sn74LS10 | 1
U14, U50 | SN74ALS86N (КР1533ЛП5) | 74xx/74ls86.pdf | 2
U15, U17 | CD4520АN (К561ИЕ10A) | http://www.intersil.com/content/dam/Intersil/documents/cd45/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 | 2
U16 | SN74ALS257N_(КР1533КП11А) | http://www.ti.com/lit/gpn/sn74LS257 | 1
U18 | CD4011 (К561ЛА7) | http://www.intersil.com/content/dam/Intersil/documents/cd40/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 | 1
U21 | SN74ALS14 (КР1533ТЛ2) | http://www.ti.com/lit/gpn/sn74LS14 | 1
U22, U25, U55, U62 | 74LS257 (КР1533КП11А) | http://www.ti.com/lit/gpn/sn74LS257 | 4
U23, U24, U26, U27 | SN74ALS253N (КР1533КП12) | http://www.ti.com/lit/gpn/sn74LS253 | 4
U28, U29, U39, U75 | IN74ALS32N (КР1533ЛЛ1) | http://www.ti.com/lit/gpn/sn74LS32 | 4
U31-U38 | RU5D1 |  | 8
U41-U48 | 2118 (КР565РУ6) |  | 8
U51 | SN7486N (К155ЛП5) | 74xx/74ls86.pdf | 1
U52, U56, U59, U63, U66 | SN74ALS175N (КР1533ТМ8) | http://www.ti.com/lit/gpn/sn74LS175 | 5
U53, U60 | SN74ALS153N (КР1533КП2) | http://www.ti.com/lit/gpn/sn74LS153 | 2
U54, U61 | SN74ALS298N (КР1533КП13) | http://www.ti.com/lit/gpn/sn74LS298 | 2
U57, U58, U64, U65 | SN74LS295N_(К555ИР16) | http://www.ti.com/lit/gpn/sn74LS295 | 4
U67 | 8282 (КР580ИР82) |  | 1
U68, U72 | КР556РТ2 |  | 2
U69 | Z80CPU | www.zilog.com/manage_directlink.php?filepath=docs/z80/um0080 | 1
U70, U71 | 27C64 | http://ww1.microchip.com/downloads/en/devicedoc/11003L.pdf | 2
Y1 | 14 MHz | ~ | 1
